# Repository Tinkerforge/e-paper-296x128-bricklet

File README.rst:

ePaper 128x296 Bricklet
========================

This repository contains the firmware source code and the hardware design
files. The documentation generator configs can be found at
https://github.com/Tinkerforge/generators

Repository Content
------------------

software/:
 * examples/: Examples for all supported languages
 * build/: Compiled files
 * src/: Source code of firmware
 * Makefile: Makefile to build project

hardware/:
 * Contains KiCad project files and additionally schematics as PDF

datasheets/:
 * Contains datasheets for sensors and complex ICs that are used

Hardware
--------

The hardware is designed with the open source EDA Suite KiCad
(http://www.kicad.org). Before you are able to open the files,
you have to install the Tinkerforge kicad-libraries
(https://github.com/Tinkerforge/kicad-libraries). You can either clone
them directly in hardware/ or clone them in a separate folder and
symlink them into hardware/
(ln -s kicad_path/kicad-libraries project_path/hardware). After that you
can open the .pro file in hardware/ with KiCad and from there view and
modify the schematics and the PCB layout.

Software
--------

If you want to do your own Brick/Bricklet firmware development we highly
recommend that you use our build environment setup script and read the
tutorial (https://www.tinkerforge.com/en/doc/Tutorials/Tutorial_Build_Environment/Tutorial.html).

To compile the C code we recommend you to install the newest GNU Arm Embedded
Toolchain (https://launchpad.net/gcc-arm-embedded/+download).
You also need to install bricklib2 (https://github.com/Tinkerforge/bricklib2).

You can either clone it directly in software/src/ or clone it in a
separate folder and symlink it into software/src/
(ln -s bricklib_path/bricklib2 project_path/software/src/). Finally make sure to
have CMake installed (http://www.cmake.org/cmake/resources/software.html).

After that you can build the firmware by invoking make in software/.
The firmware (.zbin) can then be found in software/build/ and uploaded
with brickv (click button "Flashing" on start screen).

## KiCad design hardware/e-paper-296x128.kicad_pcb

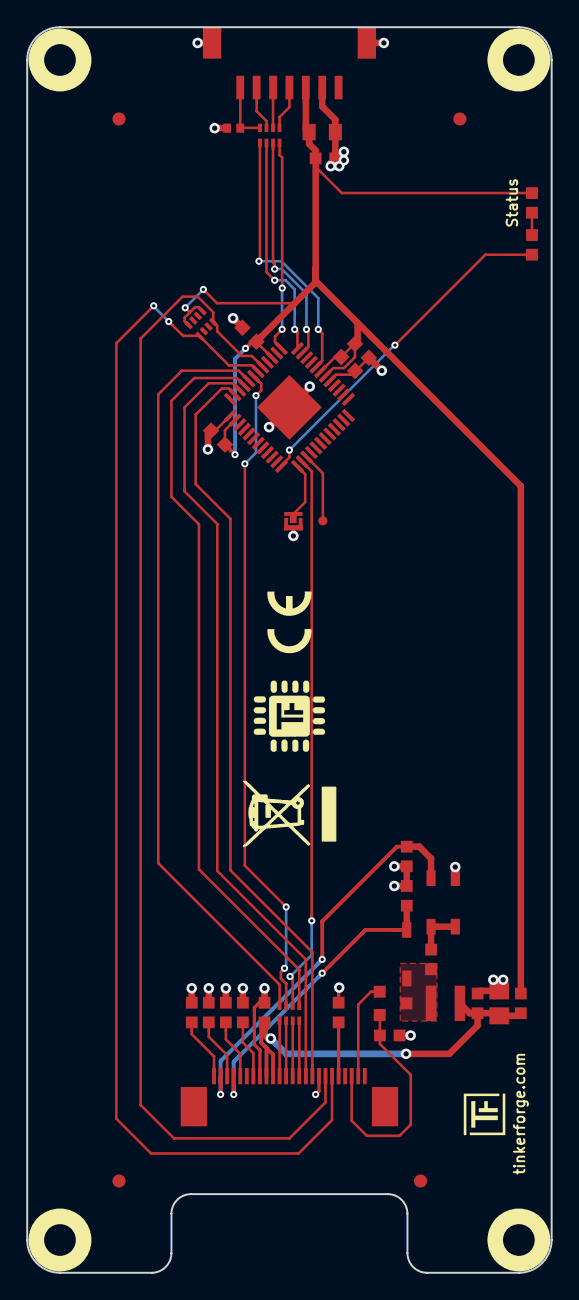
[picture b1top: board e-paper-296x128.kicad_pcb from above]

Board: 2 copper layers, 40.0 x 95.0 mm, 45 parts (0 on the bottom side), 38 nets.

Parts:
C1: 220pF; C0402F
C2, C4, C5, C9, C17: 1uF; C0603F
C3: 10uF; C0805
C6, C12, C13: 100nF; C0603F
C7: 1uF/10V; C0603F
C8: 4,7uF/10V; C0603F
C10, C11, C15: 1uF/25V; C0603F
C14: 220nF; C0603F
C16: 0,47uF/25V; C0603F
C18: 10uF; C0805E
D1: blue; D0603F
D2, D3, D4: B0520LW; SOD-123
Fiducial_Mark: VAL**; Fiducial_Mark
Fiducial_Mark#2, Fiducial_Mark#3, Fiducial_Mark#4: VAL**; Fiducial_Mark
L1: NR3015T4R7M; NRH3015
L2: FB; R0603F
P1: CON-SENSOR; CON-SENSOR2
P4: BOOT; SolderJumper
P5: DEBUG; DEBUG_PAD
Q1: 2N7002P; SOT23GDS
R1: 2,2; R0603F
R2: 1k; R0603F
RP1: 82; 4X0402
RP2: 4,7k; 4X0402
RP101: 220; 4X0402
U1: XMC1404; QFN48-EP2
U2: Con24HT; ER-CON24HT-1
U4, U5, U6, U7: DRILL; DRILL_NP
VAL: CE_5mm
VAL#2: WEEE_7mm

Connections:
3V3: C3.2, C4.2, C6.2, C12.2, C13.2, C14.2, D1.1, L2.1, P1.3, RP2.1, RP2.4, U1.18, U1.19, U1.27, U1.38
+VSW: C9.2, D3.1, L1.1, Q1.D
BUSY: U1.35, U2.9
CLK: RP101.7, U1.31
CS#: RP101.6, U1.2
DC#: RP101.5, U1.33
GDR: Q1.G, U2.2
GND: C1.1, C2.1, C3.1, C4.1, C5.1, C6.1, C7.1, C8.2, C10.2, C11.2, C12.1, C13.1, C14.1, C15.2, C16.2, C17.2, C18.2, D4.2, P1.2, P1.EP, P4.1, R1.2, U1.17, U1.37, U1.EP, U2.8, U2.17
MISO_MOSI: RP101.8, U1.32
unnamed: C1.2, P1.7, RP1.4
unnamed: C7.2, U2.18
unnamed: C9.1, D2.2, D4.1
unnamed: C10.1, U2.20
unnamed: C11.1, U2.5
unnamed: C15.1, U2.22
unnamed: C16.1, U2.24
unnamed: D1.2, R2.2
unnamed: P1.4, RP1.1
unnamed: P1.5, RP1.2
unnamed: P1.6, RP1.3
unnamed: P4.2, U1.1
unnamed: P5.1, U1.3
unnamed: R2.1, U1.48
unnamed: RP101.1, U2.14
unnamed: RP101.2, U2.13
unnamed: RP101.3, U2.12
unnamed: RP101.4, U2.11
RES#: U1.34, U2.10
RESE: Q1.S, R1.1, U2.3
S-CLK: RP1.7, U1.23
S-CS: RP1.8, U1.25
S-MISO: RP1.5, U1.20
S-MOSI: RP1.6, U1.24
TSCL: RP2.5, U1.30, U2.6
TSDA: RP2.8, U1.29, U2.7
VCI: C8.1, C17.1, C18.1, L1.2, L2.2, U2.15, U2.16
VGH: C2.2, D3.2, U2.21
VGL: C5.2, D2.1, U2.23

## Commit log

2018-09-28 initial push/ schematic template
2018-09-28 created schematic
2018-09-28 changed schematic
2018-09-28 added pcb layout / changed SPI Pins to display
2018-10-24 pcb design
2018-10-24 change pcb an schematic design
2018-10-24 changed schematic and pcb design
2018-10-24 final prototype design
2018-10-25 fix text size
2019-01-07 add hint
2019-01-17 shrink board by 5mm
2019-01-17 add fiducials, add spi serial resistor
2019-01-22 drc check
2019-03-06 Add initial version of E-Paper API and driver
2019-03-06 Add support for delta mode that uses internal buffers
2019-03-06 If we turn delta mode off again, zero red buffer
2019-03-06 Remove custom mode
2019-03-06 Simplify draw function
2019-03-06 Remove unused check
2019-03-06 Add display type API
2019-03-06 Add gray color define
2019-03-06 Spaces -> Tabs
2019-03-06 Use spaces only in "LUT ascii art"
    To be sure that it is properly readable in any editor
2019-03-06 Rename "Red" to "Color"
    The secondary color can be either red or gray.
    We keep the function name agnostic about the actual color.
2019-03-28 mqtt: Fix whitespace.
2019-03-28 Add examples.
2019-04-03 Use 1.5MHz baudrate
2019-04-03 Handle underflow condition in draw_text function
2019-04-04 Add image load + display example for Python
2019-04-04 Remove unused imports
2019-04-05 Move example image to main examples folder
    This will be linked from all language examples
2019-04-05 Add download link for example image
2019-04-10 Use new color writing function name (write_color)
2019-04-10 Fix UID comment
2019-04-10 Add LoadImage-Examplef for C#
2019-04-10 Add LoadImage-Example for VB.NET
2019-04-10 Add load image example for C
2019-04-10 Add LoadImage-Example for java
2019-04-10 Remove accidentially copied comment
2019-04-10 Add load image example for perl
2019-04-10 Add LoadImage-example for PHP
2019-04-11 add load image example for rust
2019-04-12 Fix rust image comment (was copied from C)
2019-04-12 Add load image example for go
2019-04-15 Add Cargo.toml dependency comment
2019-04-15 Don't mix tabs and spaces
2019-04-17 Rename get/set_display to get/set_display_type
2019-04-30 Turn logging off
2019-05-09 add schematic and sym lib table
2019-05-10 add e paper display footprint
2019-05-13 add display 3d model
2019-05-13 add 3d data
2019-05-15 fix file names
2019-05-20 Release Bricklet
2019-05-28 Improve SPI IRQ performance
    Use local pointer to save the time for accessing the struct
2019-05-29 Increase version for new release (changes in bricklib2)
2019-05-29 Add rev to changelog
2019-08-13 Add updated font editor
2020-01-13 examples: Use python3 input instead of python2 raw_input.
2020-01-13 examples: mqtt: Remove trailing whitespace.
2020-01-14 examples: Use python3 input by default.
2020-03-16 Whitespace
2020-04-03 Add openHAB examples.
2020-04-07 examples: rust: Always block when calling bindings functions.
2020-08-19 Add uc examples.
2020-08-25 uc: Fix whitespace
2020-08-27 uc: Fix warnings.
2020-09-02 uc: Add example driver note.
2021-04-13 Add delta-mode support for FillDisplay-function
2021-04-13 Add ref for 2.0.2
2021-06-01 Add support for new driver chip (SSD1680)
2021-06-01 Add rev for v2.0.3
2021-06-09 Fix fading image bug after power-down
    SSD1680 needs to power-down/power-up between writes,
    otherwise the image does not stay if power is removedSSD1680 needs to
2021-06-09 Add rev for 2.0.4
2021-10-25 Update KiCad link
    https://www.kicad.org/blog/2021/10/Avoid-links-to-former-kicad-domain/
2021-12-22 Fix delta-mode for SSD1680 with new specific LUT
2021-12-22 Add rev for 2.0.5
2021-12-22 Add SSD1680 datasheet
2021-12-28 Make sure delta-mode works all of the time
    There is some kind of race-condition with the power down sequenze
    that i can't completely figure out.
    However, it turns out that the power up sequenze itself is enough to
    make sure that the image doesn't fade out if power is removed.
    There is no relevant power saving with the power down of the
    SSD1680, so we just remove the power down sequenze.
2021-12-28 Add rev for 2.0.6
2022-03-07 Add code page 437 hint
2022-04-19 examples: uc: Rename TF_HalContext to TF_HAL.
2022-04-27 uc: Adapt to bindings changes
2022-07-06 Add license files.
2023-01-23 New standart layout. Switched to Kicad 6
2025-10-04 Fix compatibility with new Docker build image (GCC 14.2.1)

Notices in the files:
hardware/e-paper-296x128.kicad_pcb:
Copyright Tinkerforge GmbH 2018.
This documentation describes Open Hardware and is licensed under the
CERN OHL v. 1.1.
